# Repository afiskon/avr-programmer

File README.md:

# avr-programmer
Simple AVR programmer based on ATmega328P and FT232

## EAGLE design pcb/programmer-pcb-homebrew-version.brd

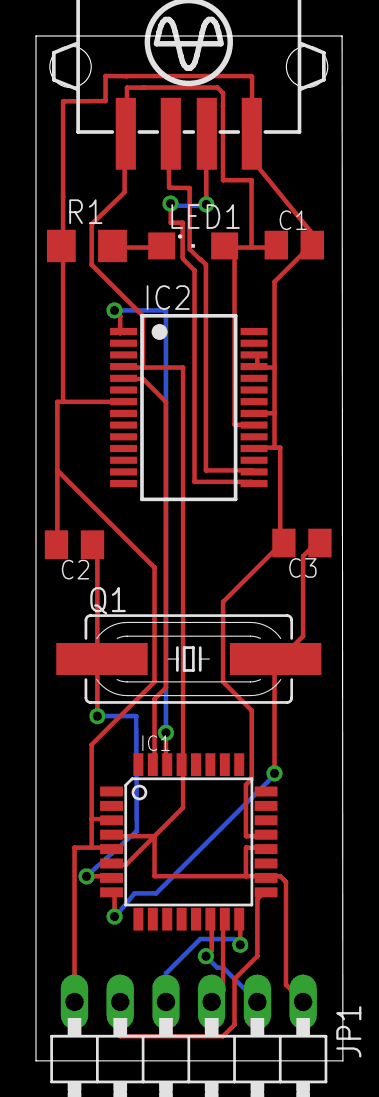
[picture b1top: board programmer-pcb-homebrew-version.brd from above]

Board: 2 copper layers, 17.0 x 56.9 mm, 10 parts (0 on the bottom side), 13 nets.

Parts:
C1: 100 uF; C0805K
C2, C3: 22 pF; C0805K
IC1: MEGA8-AI; TQFP32-08
IC2: FT232RL; SSOP28
JP1: 1X06/90
LED1: SML1206
Q1: 16 MHz; SM49
R1: 1k; R1206
X1: USB-A003

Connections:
GND: C2.2, IC1.3, IC1.5, IC2.7, JP1.6, R1.1
unnamed: LED1.C, R1.2
unnamed: C2.1, Q1.1
unnamed: C3.1, Q1.2
unnamed: IC1.30, IC2.1
unnamed: IC1.31, IC2.5
unnamed: IC1.16, JP1.4
unnamed: IC1.15, JP1.3
unnamed: IC1.14, JP1.2
unnamed: IC1.17, JP1.5
S$1: C1.2, C3.2, IC1.21, IC2.18, IC2.21, IC2.25, IC2.26
S$6: C1.1, IC2.20, LED1.A
VCC: IC1.4, IC1.6, IC1.18, IC1.20, IC1.29, IC2.4, JP1.1

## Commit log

2017-01-26 Project moved from a sandbox repository
2017-01-27 Firmware added + minor changes
2017-02-13 Added PCB version that better fits for making it at home
2017-02-13 Minor changes
2017-02-15 Revert "Minor changes"
    This reverts commit 5d468dcfe678118c8d189d65b8291410209d50cf.
2017-02-15 Revert "Added PCB version that better fits for making it at home"
    This reverts commit 82dccade7066e91744d8b01686318e8a82b5671a.
